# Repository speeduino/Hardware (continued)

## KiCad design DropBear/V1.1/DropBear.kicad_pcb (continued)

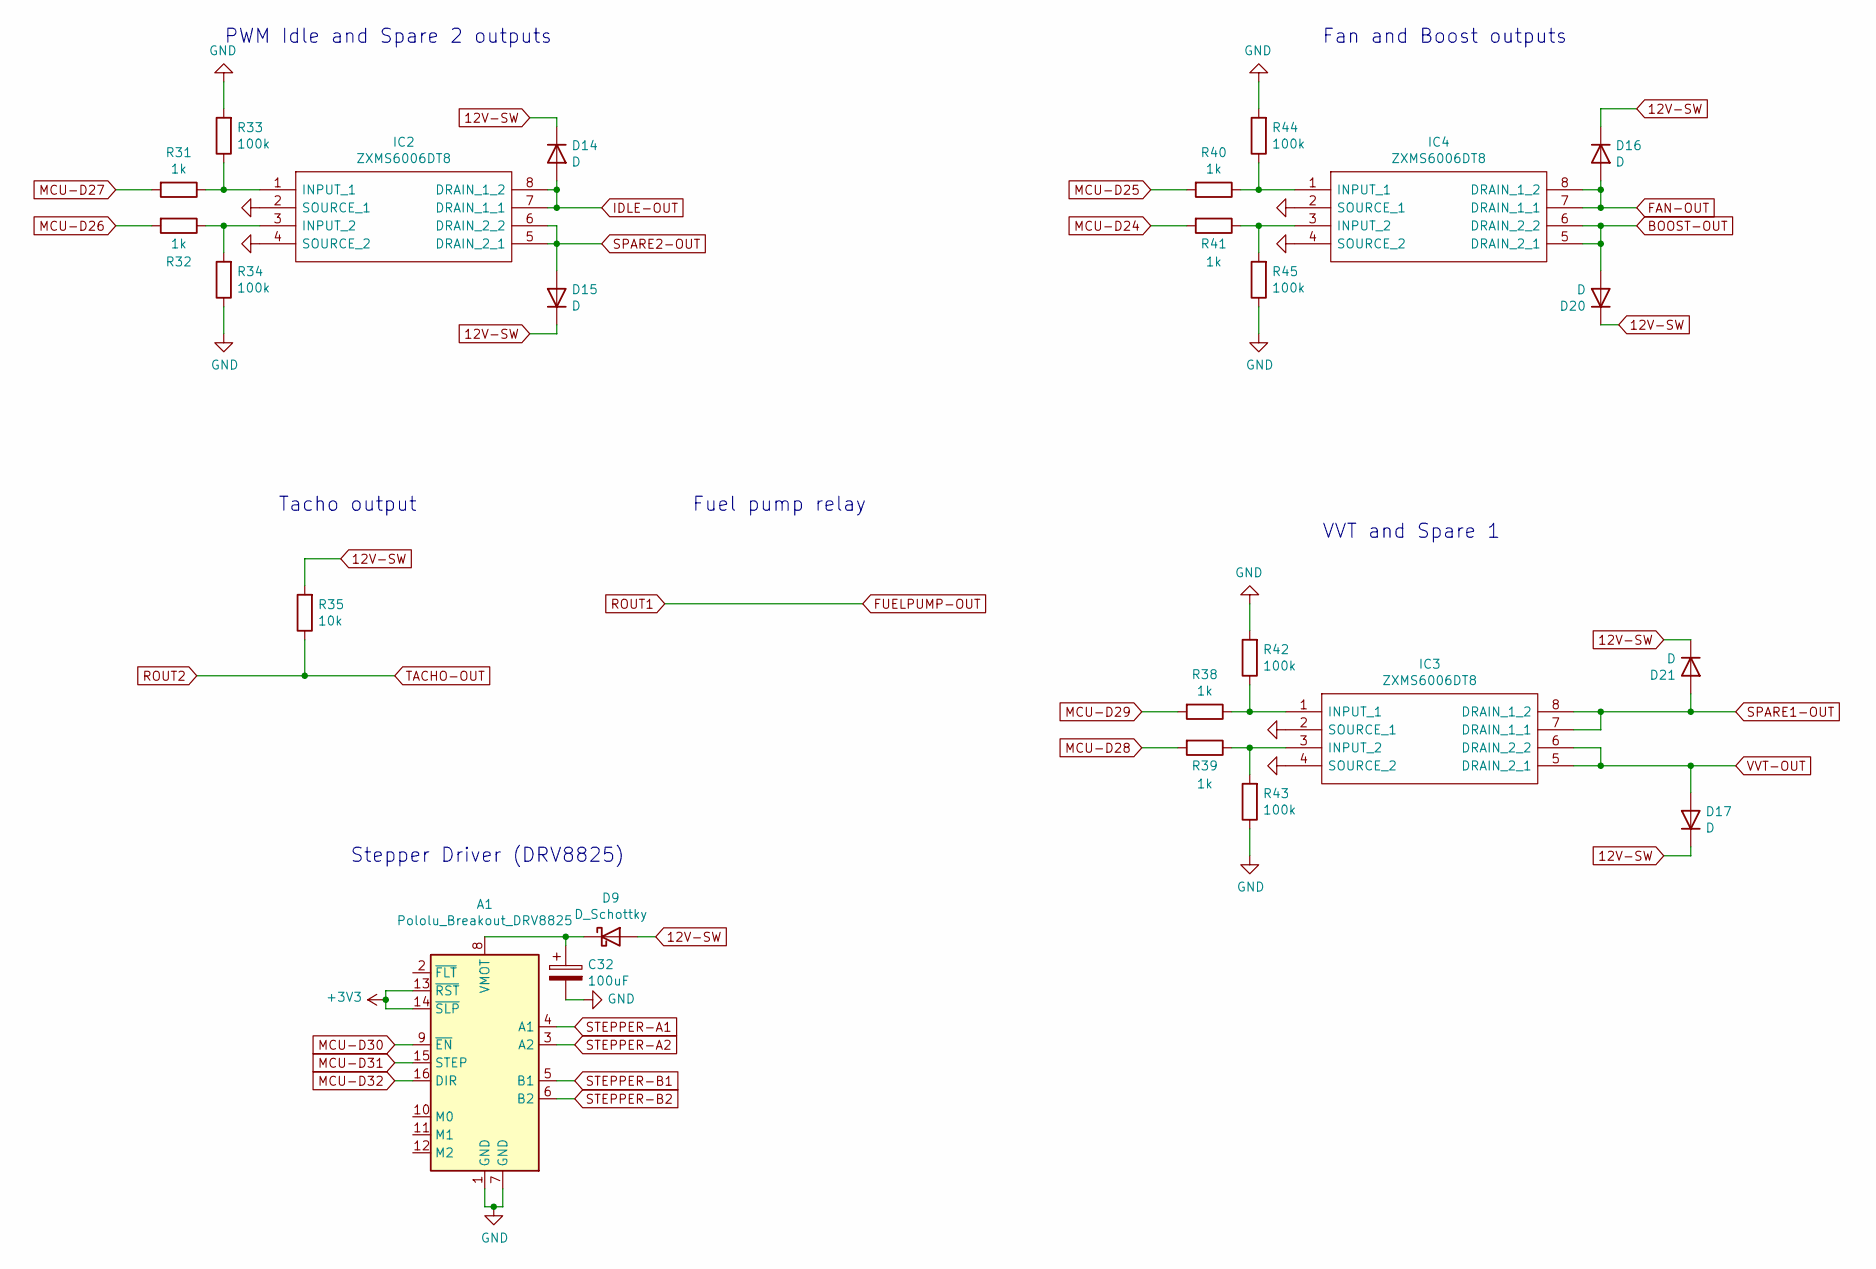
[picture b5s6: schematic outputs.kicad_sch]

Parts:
A1: Pololu_Breakout_DRV8825; Pololu_Breakout-16_15.2x20.3mm
C32: 100uF; CP_Elec_6.3x7.7; Manufacturer_Part_Number EEE-FT1V101AV; Digikey Part Number P124821CT-ND
D9: D_Schottky; D_PowerDI-123; Manufacturer_Part_Number DFLS2100-7; Digikey Part Number DFLS2100-7DICT-ND
D14, D15, D16, D17, D20, D21: D; D_SOD-323; Manufacturer_Part_Number 1N4448WX-TP; Digikey Part Number 1N4448WXTPMSCT-ND
IC2, IC3, IC4: ZXMS6006DT8; Diodes_SM8; Manufacturer_Part_Number ZXMS6006DT8; Digikey Part Number ZXMS6006DT8TADICT-ND
R31, R32, R38, R39, R40, R41: 1k; R_0805_2012Metric_Pad1.15x1.40mm_HandSolder; Manufacturer_Part_Number RC0805FR-071KL; Digikey Part Number 311-1.00KCRCT-ND
R33, R34, R42, R43, R44, R45: 100k; R_0805_2012Metric_Pad1.15x1.40mm_HandSolder; Manufacturer_Part_Number RC0805FR-07100KL; Digikey Part Number 311-100KCRCT-ND
R35: 10k; R_0805_2012Metric; Manufacturer_Part_Number RC0805JR-0710KL; Digikey Part Number 311-10KARCT-ND

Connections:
12V-SW: D9.2 (A), D14.1 (K), D15.1 (K), D16.1 (K), D17.1 (K), D20.1 (K), D21.1 (K), R35.2; also elsewhere on the board
+3V3: A1.13 (~RST), A1.14 (~SLP); also elsewhere on the board
BOOST-OUT: D20.2 (A), IC4.5 (DRAIN_2_1), IC4.6 (DRAIN_2_2); also elsewhere on the board
FAN-OUT: D16.2 (A), IC4.7 (DRAIN_1_1), IC4.8 (DRAIN_1_2); also elsewhere on the board
GND: A1.1 (GND), A1.7 (GND), C32.2, IC2.2 (SOURCE_1), IC2.4 (SOURCE_2), IC3.2 (SOURCE_1), IC3.4 (SOURCE_2), IC4.2 (SOURCE_1), IC4.4 (SOURCE_2), R33.2, R34.1, R42.2, R43.1, R44.2, R45.1; also elsewhere on the board
IDLE-OUT: A1.5 (B1), D14.2 (A), IC2.7 (DRAIN_1_1), IC2.8 (DRAIN_1_2); also elsewhere on the board
MCU-D24: R41.2; also elsewhere on the board
MCU-D25: R40.2; also elsewhere on the board
MCU-D26: R32.2; also elsewhere on the board
MCU-D27: R31.2; also elsewhere on the board
MCU-D28: R39.2; also elsewhere on the board
MCU-D29: R38.2; also elsewhere on the board
MCU-D30: A1.9 (~EN); also elsewhere on the board
MCU-D31: A1.15 (STEP); also elsewhere on the board
MCU-D32: A1.16 (DIR); also elsewhere on the board
unnamed: A1.8 (VMOT), C32.1, D9.1 (K)
unnamed: IC2.1 (INPUT_1), R31.1, R33.1
unnamed: IC2.3 (INPUT_2), R32.1, R34.2
unnamed: IC3.1 (INPUT_1), R38.1, R42.1
unnamed: IC3.3 (INPUT_2), R39.1, R43.2
unnamed: IC4.1 (INPUT_1), R40.1, R44.1
unnamed: IC4.3 (INPUT_2), R41.1, R45.2
ROUT2: R35.1; also elsewhere on the board
SPARE1-OUT: A1.3 (A2), D21.2 (A), IC3.7 (DRAIN_1_1), IC3.8 (DRAIN_1_2); also elsewhere on the board
SPARE2-OUT: A1.6 (B2), D15.2 (A), IC2.5 (DRAIN_2_1), IC2.6 (DRAIN_2_2); also elsewhere on the board
STEPPER-A1: A1.4 (A1), D17.2 (A), IC3.5 (DRAIN_2_1), IC3.6 (DRAIN_2_2); also elsewhere on the board

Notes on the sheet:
Fan and Boost outputs
Fuel pump relay
PWM Idle and Spare 2 outputs
Tacho output
VVT and Spare 1
Stepper Driver (DRV8825)

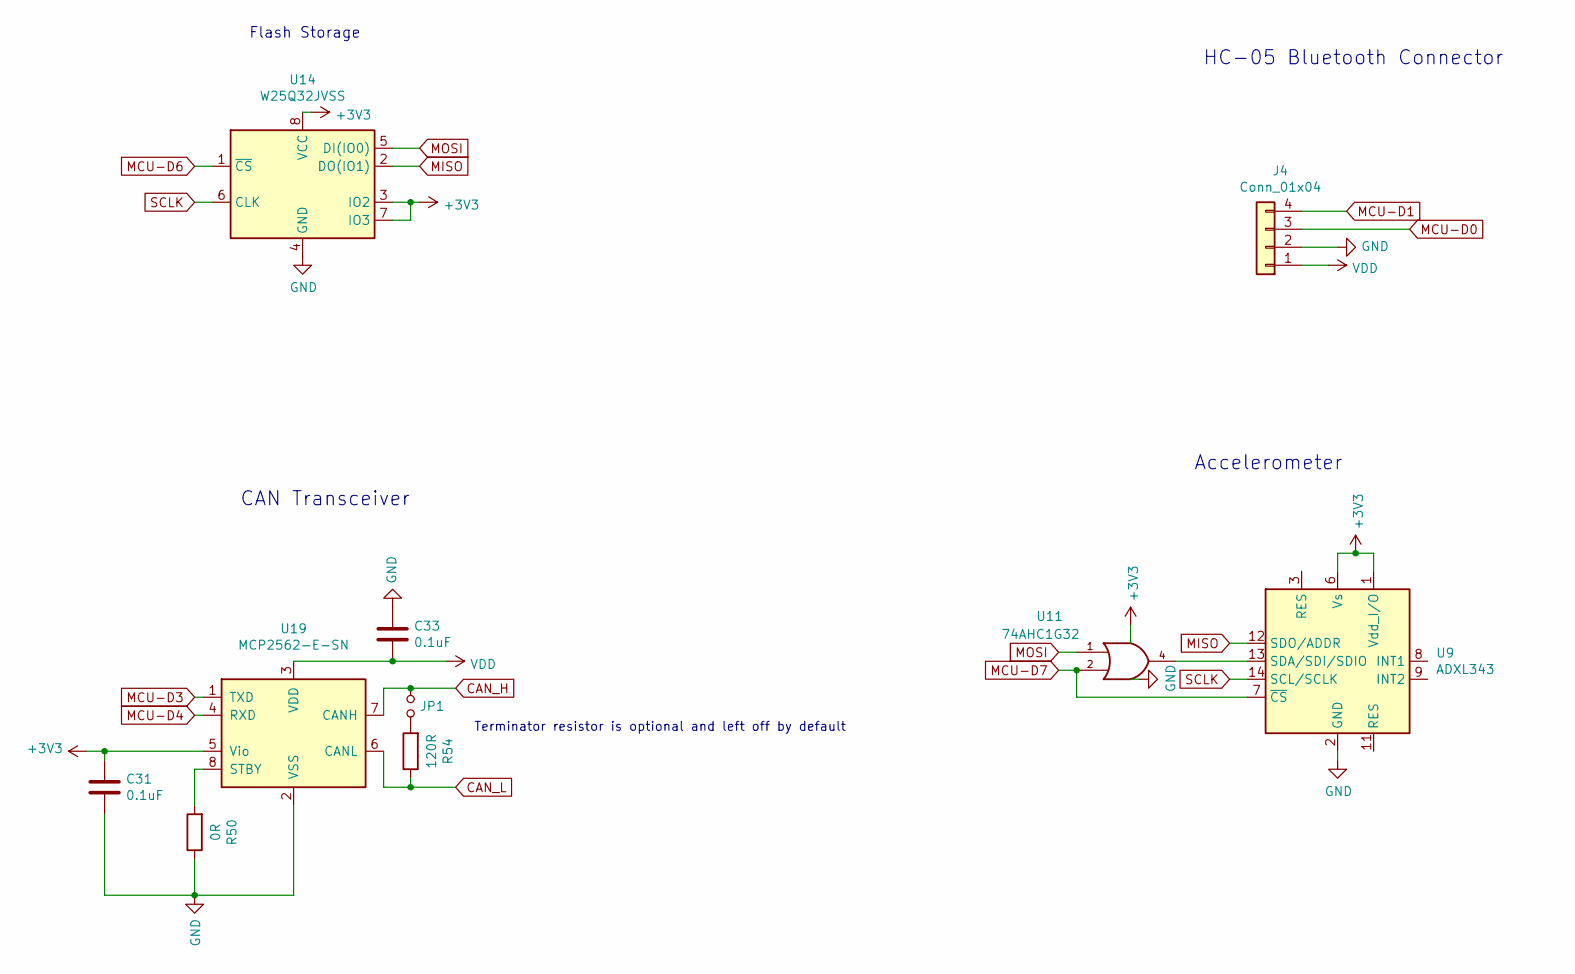
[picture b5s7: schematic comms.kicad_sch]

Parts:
C31, C33: 0.1uF; C_0805_2012Metric; Manufacturer_Part_Number CC0805KRX7R9BB104; Digikey Part Number 311-1140-1-ND
J4: Conn_01x04; PinHeader_1x04_P2.54mm_Vertical
JP1: Jumper_NO_Small; SolderJumper-2_P1.3mm_Open_Pad1.0x1.5mm
R50: 0R; R_0805_2012Metric_Pad1.15x1.40mm_HandSolder; Manufacturer_Part_Number RC0805JR-070RL; Digikey Part Number 311-0.0ARCT-ND
R54: 120R; R_0805_2012Metric_Pad1.15x1.40mm_HandSolder; Manufacturer_Part_Number RC0805FR-07120RL; Digikey Part Number 311-120CRCT-ND
U9: ADXL343; LGA-14_3x5mm_P0.8mm_LayoutBorder1x6y; Manufacturer_Part_Number ADXL343BCCZ-RL; Digikey Part Number ADXL343BCCZ-RLCT-ND
U11: 74AHC1G32; SOT-353_SC-70-5; Manufacturer_Part_Number SN74AHC1G32DCKR; Digikey Part Number 296-8749-1-ND
U14: W25Q32JVSS; SOIC-8_5.23x5.23mm_P1.27mm; Manufacturer_Part_Number W25Q32JVSSIQ; Digikey Part Number W25Q32JVSSIQCT-ND
U19: MCP2562-E-SN; SOIC-8_3.9x4.9mm_P1.27mm; Manufacturer_Part_Number MCP2562-E/SN; Digikey Part Number MCP2562-E/SN-ND

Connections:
+3V3: C31.1, U9.1 (Vdd_I/O), U9.6 (Vs), U11.5 (VCC), U14.3 (IO2), U14.7 (IO3), U14.8 (VCC), U19.5 (Vio); also elsewhere on the board
+5V: C33.2, J4.1, U19.3 (VDD); also elsewhere on the board
CAN_H: JP1.1, U19.7 (CANH); also elsewhere on the board
CAN_L: R54.1, U19.6 (CANL); also elsewhere on the board
GND: C31.2, C33.1, J4.2, R50.1, U9.2 (GND), U9.4 (GND), U9.5 (GND), U11.3 (GND), U14.4 (GND), U19.2 (VSS); also elsewhere on the board
MCU-D0: J4.3; also elsewhere on the board
MCU-D1: J4.4; also elsewhere on the board
MCU-D3: U19.1 (TXD); also elsewhere on the board
MCU-D4: U19.4 (RXD); also elsewhere on the board
MCU-D6: U14.1 (~CS); also elsewhere on the board
MCU-D7: U9.7 (~CS), U11.2; also elsewhere on the board
MISO: U9.12 (SDO/ADDR), U14.2 (DO(IO1)); also elsewhere on the board
MOSI: U11.1, U14.5 (DI(IO0)); also elsewhere on the board
unnamed: JP1.2, R54.2
unnamed: R50.2, U19.8 (STBY)
unnamed: U9.13 (SDA/SDI/SDIO), U11.4
SCLK: U9.14 (SCL/SCLK), U14.6 (CLK); also elsewhere on the board

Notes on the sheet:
Terminator resistor is optional and left off by default
Accelerometer
Flash Storage
CAN Transceiver
HC-05 Bluetooth Connector

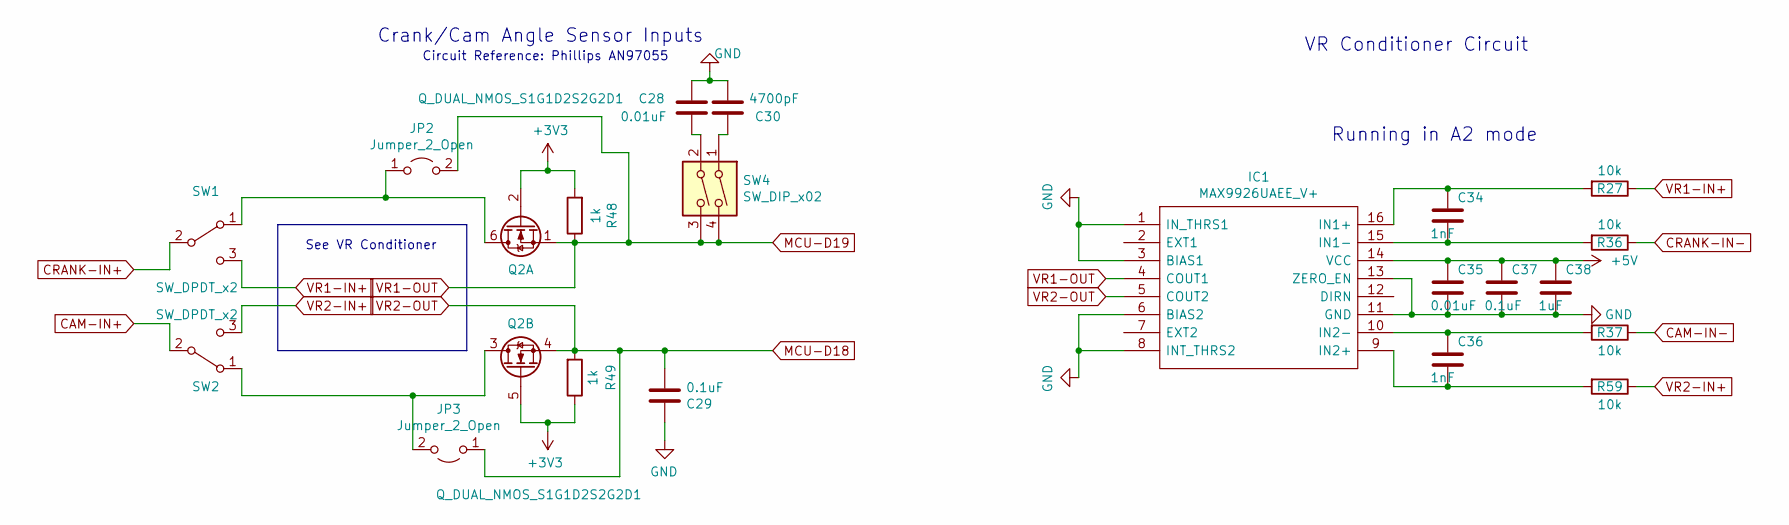
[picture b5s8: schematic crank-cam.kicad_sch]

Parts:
C28, C35: 0.01uF; C_0805_2012Metric; Manufacturer_Part_Number CC0805KRX7R9BB103; Digikey Part Number 311-1136-1-ND
C29, C37: 0.1uF; C_0805_2012Metric; Manufacturer_Part_Number CC0805KRX7R9BB104; Digikey Part Number 311-1140-1-ND
C30: 4700pF; C_0805_2012Metric; Manufacturer_Part_Number CC0805KRX7R9BB472; Digikey Part Number 311-1133-1-ND
C34, C36: 1nF; C_0805_2012Metric; Manufacturer_Part_Number C0805C102J5HACAUTO; Digikey Part Number 399-16591-1-ND
C38: 1uF; C_0805_2012Metric; Manufacturer_Part_Number CC0805KKX7R7BB105; Digikey Part Number 311-1365-1-ND
IC1: MAX9926UAEE_V+; QSOP-16_3.9x4.9mm_P0.635mm; Manufacturer_Part_Number MAX9926UAEE/V+; Mouser Part Number 700-MAX9926UAEE/V+
JP2, JP3: Jumper_2_Open; SolderJumper-2_P1.3mm_Open_Pad1.0x1.5mm
Q2: Q_DUAL_NMOS_S1G1D2S2G2D1; SOT-363_SC-70-6; Manufacturer_Part_Number NVJD5121NT1G; Digikey Part Number NVJD5121NT1GOSCT-ND
R27, R36, R37, R59: 10k; R_1206_3216Metric; Manufacturer_Part_Number RC1206FR-7W10KL; Digikey Part Number 13-RC1206FR-7W10KLTR-ND
R48, R49: 1k; R_0805_2012Metric; Manufacturer_Part_Number RC0805FR-071KL; Digikey Part Number 311-1.00KCRCT-ND
SW1, SW2: SW_DPDT_x2; AYZ0202AGRLC; Manufacturer_Part_Number AYZ0202AGRLC; Digikey Part Number 401-2013-1-ND
SW4: SW_DIP_x02; SW_DIP_SPSTx02_Slide_9.78x7.26mm_W8.61mm_P2.54mm; Manufacturer_Part_Number IKN0204000; Digikey Part Number 679-3566-1-ND

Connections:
+3V3: Q2.2 (G), Q2.5 (G), R48.2, R49.1; also elsewhere on the board
+5V: C35.1, C37.1, C38.1, IC1.14 (VCC); also elsewhere on the board
CAM-IN+: SW2.2 (B); also elsewhere on the board
CAM-IN-: R37.1; also elsewhere on the board
CRANK-IN+: SW1.2 (B); also elsewhere on the board
CRANK-IN-: R36.1; also elsewhere on the board
GND: C28.1, C29.1, C30.2, C35.2, C37.2, C38.2, IC1.1 (IN_THRS1), IC1.3 (BIAS1), IC1.6 (BIAS2), IC1.8 (INT_THRS2), IC1.11 (GND), IC1.13 (ZERO_EN); also elsewhere on the board
MCU-A4: C29.2, IC1.5 (COUT2), JP3.1 (A), Q2.4 (S), R49.2; also elsewhere on the board
MCU-A5: IC1.4 (COUT1), JP2.2 (B), Q2.1 (S), R48.1, SW4.3, SW4.4; also elsewhere on the board
unnamed: C28.2, SW4.2
unnamed: C30.1, SW4.1
unnamed: C34.1, IC1.16 (IN1+), R27.2
unnamed: C34.2, IC1.15 (IN1-), R36.2
unnamed: C36.1, IC1.10 (IN2-), R37.2
unnamed: C36.2, IC1.9 (IN2+), R59.2
unnamed: JP2.1 (A), Q2.6 (D), SW1.1 (A)
unnamed: JP3.2 (B), Q2.3 (D), SW2.1 (A)
VR1-IN+: R27.1, SW1.3 (C)
VR2-IN+: R59.1, SW2.3 (C)

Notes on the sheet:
Running in A2 mode
VR Conditioner Circuit
Crank/Cam Angle Sensor Inputs
See VR Conditioner
Circuit Reference: Phillips AN97055

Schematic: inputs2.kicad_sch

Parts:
C39, C40: 0.01uF; C_0805_2012Metric; Manufacturer_Part_Number CC0805KRX7R9BB103; Digikey Part Number 311-1136-1-ND
Q3: Q_DUAL_NMOS_S1G1D2S2G2D1; SOT-363_SC-70-6; Manufacturer_Part_Number NVJD5121NT1G; Digikey Part Number NVJD5121NT1GOSCT-ND
R55, R57: 180k; R_0805_2012Metric; Manufacturer_Part_Number RC0805FR-07180KL; Digikey Part Number 311-180KCRCT-ND
R56, R58: 348k; R_0805_2012Metric; Manufacturer_Part_Number ERJ-6ENF3483V; Digikey Part Number P348KCDKR-ND
R60, R61: 1k; R_0805_2012Metric; Manufacturer_Part_Number RC0805FR-071KL; Digikey Part Number 311-1.00KCRCT-ND
U20: LMV324LIDT; SOIC-14_3.9x8.7mm_P1.27mm; Manufacturer_Part_Number LMV324LIDT; Digikey Part Number 497-13052-1-ND

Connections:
+3V3: Q3.2 (G), Q3.5 (G), R60.2, R61.2; also elsewhere on the board
ADC-Clamp-3: U20.6 (-), U20.7; also elsewhere on the board
ADC-Clamp-4: U20.1, U20.2 (-); also elsewhere on the board
GND: C39.1, C40.1, R56.1, R58.1, U20.11 (V-); also elsewhere on the board
MCU-A8: C40.2, Q3.4 (S), R61.1; also elsewhere on the board
MCU-A9: C39.2, Q3.1 (S), R60.1; also elsewhere on the board
unnamed: R55.1, R56.2, U20.3 (+)
unnamed: R57.1, R58.2, U20.5 (+)
unnamed: U20.8, U20.9 (-)
unnamed: U20.13 (-), U20.14
SPARE1-Digital: Q3.6 (D); also elsewhere on the board
SPARE1_Sensor: R55.2; also elsewhere on the board
SPARE2-Digital: Q3.3 (D); also elsewhere on the board
SPARE2_Sensor: R57.2; also elsewhere on the board
VDDA: U20.4 (V+); also elsewhere on the board

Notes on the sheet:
5v to 3.3v Opamp
Second O2 sensor should be on Spare 2 if in use
Spare digital inputs

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
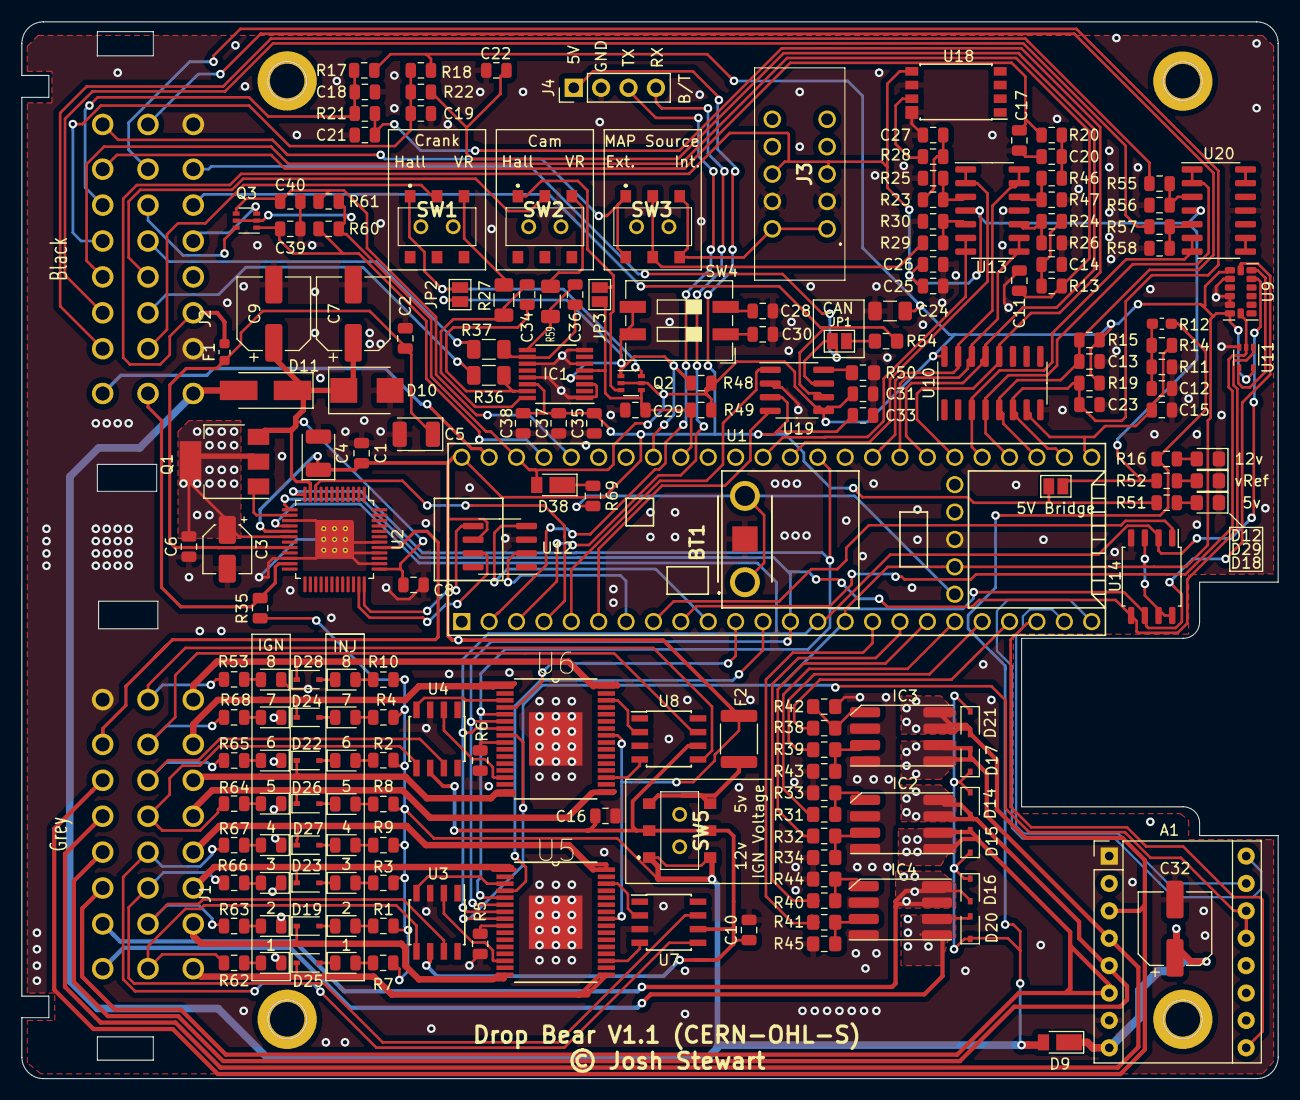
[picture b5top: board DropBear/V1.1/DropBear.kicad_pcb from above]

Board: 2 copper layers, 116.5 x 98.0 mm, 187 parts (0 on the bottom side), 165 nets.

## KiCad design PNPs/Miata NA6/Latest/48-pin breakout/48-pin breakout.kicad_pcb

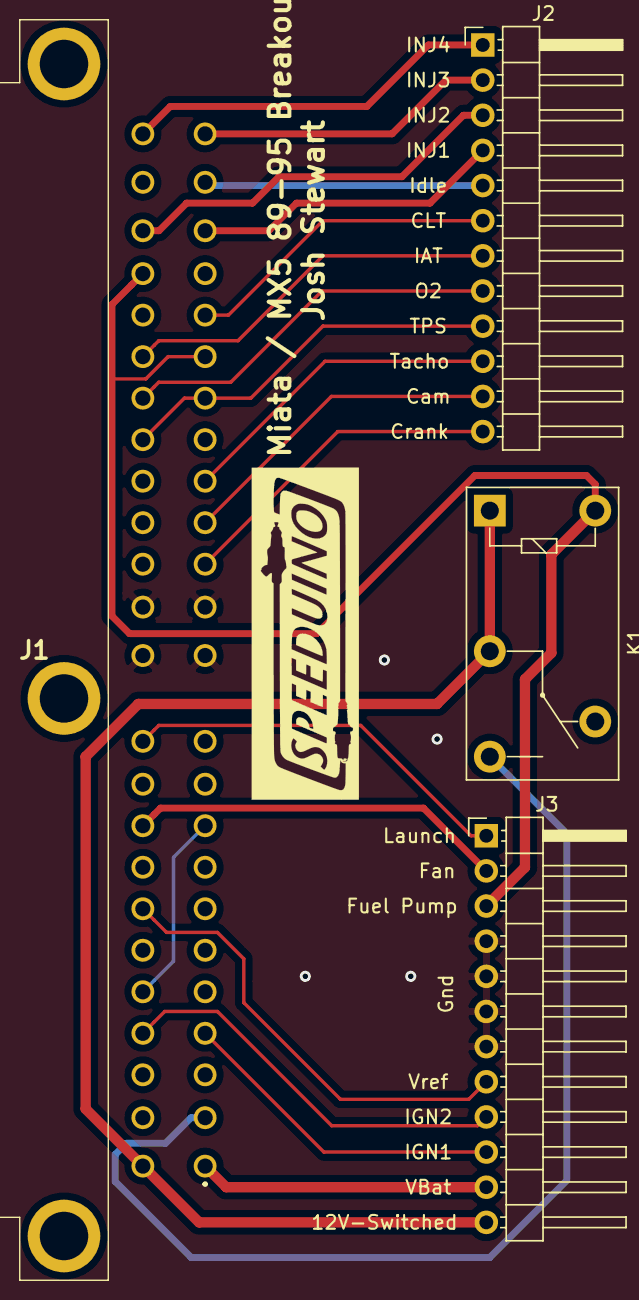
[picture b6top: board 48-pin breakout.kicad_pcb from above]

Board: 2 copper layers, 4 parts (0 on the bottom side), 23 nets.

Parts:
J1: 174917-1; 1749171
J2, J3: Conn_01x12; PinHeader_1x12_P2.54mm_Horizontal
K1: G5LE-1; Relay_SPDT_Omron-G5Q-1

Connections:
12V-SW: J1.25, J3.12, K1.1, K1.2
AC_Jump: J1.9, J1.29
CLT: J1.20, J2.6
Cam: J1.15, J2.11
Crank: J1.14, J2.12
Fan: J1.33, J3.2
GND: J1.12, J1.13, J1.36, J1.37, J3.4, J3.5, J3.6, J3.7
IAT: J1.43, J2.7
IGN-1: J1.4, J3.10
IGN-2: J1.28, J3.9
INJ-1: J1.22, J2.4
INJ-2: J1.46, J2.3
INJ-3: J1.24, J2.2
INJ-4: J1.48, J2.1
Idle: J1.23, J2.5
Launch: J1.35, J3.1
O2: J1.42, J2.8
Pump: J1.19, J1.45, J3.3, K1.5
ST_Sig: J1.2, K1.3
TPS: J1.18, J1.41, J2.9
Tacho: J1.16, J2.10
VBat: J1.1, J3.11
VRef: J1.31, J3.8

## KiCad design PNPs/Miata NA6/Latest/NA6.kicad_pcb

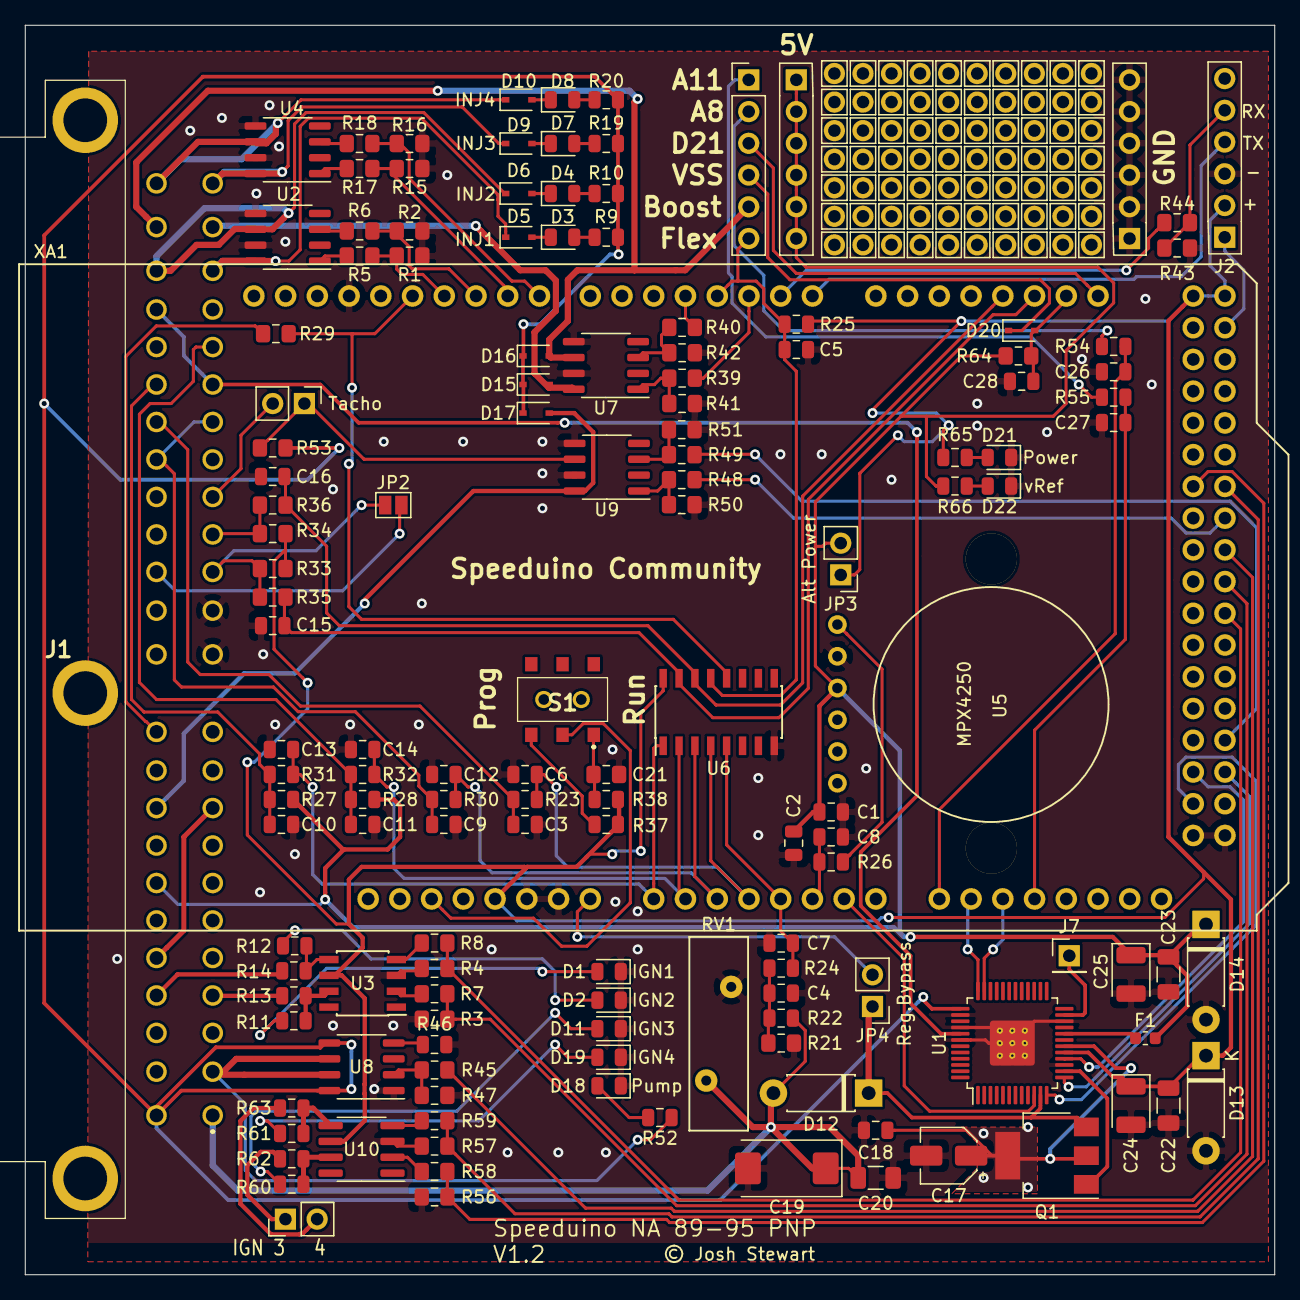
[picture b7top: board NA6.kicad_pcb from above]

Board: 2 copper layers, 100.0 x 100.0 mm, 142 parts (0 on the bottom side), 113 nets.

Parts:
C1: 0.01uF; C_0805_2012Metric
C2: 1uF; C_0805_2012Metric
C3, C4, C9, C10, C11, C15, C16, C18, C26, C27, C28: 0.1uF; C_0805_2012Metric
C5: 0.27uF; C_0805_2012Metric
C6, C7, C12, C13, C14: 0.22uF; C_0805_2012Metric
C8: 470pf; C_0805_2012Metric
C17: 22uF; CP_Elec_4x5.8
C19: 10uF; CP_EIA-7343-31_Kemet-D
C20, C22, C23: 0.1uF; C_1206_3216Metric
C21: 22uF; C_0805_2012Metric_Pad1.15x1.40mm_HandSolder
C24, C25: 47uF; CP_EIA-3528-21_Kemet-B
D1, D2, D3, D4, D7, D8, D11, D18, D19: LED; LED_0805_2012Metric
D5, D6, D9, D10, D15, D16, D17, D20: D; D_SOD-323
D12: D_Schottky; D_DO-41_SOD81_P7.62mm_Horizontal
D13, D14: D_Zener; D_DO-41_SOD81_P7.62mm_Horizontal
D21, D22: LED_Green; LED_0805_2012Metric
F1: Polyfuse; Fuse_0603_1608Metric
J1: 174917-1; 1749171
J2, J3, J4, J5: Conn_01x06; PinHeader_1x06_P2.54mm_Vertical
J6: Conn_01x02; PinHeader_1x02_P2.54mm_Vertical
J7: Conn_01x06; PinHeader_1x01_P2.54mm_Vertical
JP1: Jumper; PinHeader_1x02_P2.54mm_Vertical
JP2: Jumper; SolderJumper-2_P1.3mm_Open_Pad1.0x1.5mm
JP3, JP4: Jumper_2_Open; PinHeader_1x02_P2.54mm_Vertical
Q1: Q_PNP_BCEC; SOT-223-3_TabPin2
R1, R2, R3, R4, R15, R16, R41, R42, R47, R50, R51, R56, R57: 100k; R_0805_2012Metric_Pad1.15x1.40mm_HandSolder
R5, R6, R7, R8, R17, R18, R21, R29, R33, R34, R39, R40, R44, R45, R48, R49, R53, R58, R59, R64: 1k; R_0805_2012Metric_Pad1.15x1.40mm_HandSolder
R9, R10, R11, R12, R19, R20, R25, R60, R61: 2.4k; R_0805_2012Metric
R13, R14, R62, R63: 10R; R_0805_2012Metric
R22: 3.9k; R_0805_2012Metric
R23, R24, R26, R30, R31, R32, R54, R55, R65, R66: 470R; R_0805_2012Metric
R27, R28, R52: 2.49k; R_0805_2012Metric
R35, R36: 220R; R_0805_2012Metric_Pad1.15x1.40mm_HandSolder
R37, R46: 10k; R_0805_2012Metric
R38: 120R; R_0805_2012Metric
R43: 2k; R_0805_2012Metric_Pad1.15x1.40mm_HandSolder
RV1: Varistor; RV_Disc_D15.5mm_W4.7mm_P7.5mm
S1: AYZ0202AGRLC
U1: MC33814; LQFP-48-1EP_7x7mm_P0.5mm_EP3.6x3.6mm_ThermalVias
U2, U4, U7, U9: VNLD5090; SO-8_3.9x4.9mm_P1.27mm
U3, U10: TC4424A; SOIC-8_3.9x4.9mm_P1.27mm
U5: MPX4250
U6: SP720; SOIC-16_3.9x9.9mm_P1.27mm
U8: VN5160S-E; SO-8_3.9x4.9mm_P1.27mm
XA1: Arduino_Mega2560_Shield; Arduino_Mega2560_Shield_IO_Only

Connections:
12V-SW: D15.1, D16.1, D17.1, J1.25, R9.2, R10.2, R19.2, R20.2, R53.1, U1.37, U8.5, U8.8
33814-CSB: U1.10, XA1.A6
AC-Jump: J1.9, J1.29
ADC-Clamp-1: C13.1, R31.1, U6.1, XA1.A0
ADC-Clamp-2: C14.1, R32.1, U6.2, XA1.A1
ADC-Clamp-3: C12.1, R30.1, U6.3, XA1.A2
ADC-Clamp-4: C6.1, R23.1, U6.4, XA1.A3
ADC-Clamp-5: C7.1, R24.1, U6.5, XA1.A4
ADC-Clamp-11: R29.2, U6.12, XA1.D12
ADC-Clamp-12: C5.1, J5.6, R25.2, U6.13, XA1.D3
ADC-Clamp-13: C16.2, R36.1, U6.14, XA1.D18
ADC-Clamp-14: C15.2, R35.1, U6.15, XA1.D19
BOOST-OUT: D16.2, J1.47, J5.5, U7.6
CAM-IN: J1.15, R34.1, R36.2
CLT_Sensor: C11.1, J1.20, R28.1, R32.2
CRANK-IN: J1.14, JP2.1, R33.1, R35.2
Clutch_in: J1.35, R29.1
FAN-OUT: D17.2, J1.33, U9.8
GND: C1.1, C2.1, C3.2, C4.2, C5.2, C6.2, C7.2, C8.1, C9.2, C10.2, C11.2, C12.2, C13.2, C14.2, C15.1, C16.1, C17.2, C18.2, C19.2, C20.2, C21.2, C22.2, C23.2, C24.2, C25.2, C26.2, C27.2, C28.2, D1.1, D2.1, D11.1, D13.2, D14.2, D18.1, D19.1, D21.1, D22.1, J1.12, J1.13, J1.36, J1.37, J2.3, J4.1, J4.2, J4.3, J4.4, J4.5, J4.6, R1.2, R2.1, R3.2, R4.1, R15.2, R16.1, R21.1, R41.2, R42.1, R43.2, R46.2, R47.2, R50.2, R51.1, R56.2, R57.1, RV1.2, U1.15, U1.22, U1.38, U1.40, U1.42, U1.49, U2.5, U2.7, U3.3, U4.5, U4.7, U5.2, U6.8, U7.5, U7.7, U8.1, U9.5, U9.7, U10.3, XA1.GND1, XA1.GND2, XA1.GND3, XA1.GND5, XA1.GND6
IAT_Sensor: C10.1, J1.43, R27.1, R31.2
IDLE-OUT: D15.2, J1.23, U7.8
IGN-1-OUT: J1.4, R13.1
IGN-2-OUT: J1.28, R14.1
IGN-3-OUT: J6.1, R62.1
IGN-4-OUT: J6.2, R63.1
INJ-1-OUT: D5.1, J1.22, U2.8
INJ-2-OUT: D6.1, J1.46, U2.6
INJ-3-OUT: D9.1, J1.24, U4.8
INJ-4-OUT: D10.1, J1.48, U4.6
MCU-A5: C8.2, R26.1, XA1.A5
MCU-A8: C26.1, R54.2, XA1.A8
MCU-A9: U1.36, XA1.A9
MCU-A10: U1.35, XA1.A10
MCU-A11: C27.1, R55.1, XA1.A11
MCU-D0: J2.4, XA1.D0
MCU-D1: R44.1, XA1.D1
MCU-D2: R39.2, XA1.D2
MCU-D4: R40.2, XA1.D4
MCU-D8: R16.2, R18.2, XA1.D8
MCU-D9: R15.1, R17.2, XA1.D9
MCU-D10: R2.2, R6.2, XA1.D10
MCU-D11: R1.1, R5.2, XA1.D11
MCU-D20: C28.1, D20.2, R64.2, XA1.D20
MCU-D21: J5.3, XA1.D21
MCU-D23: J2.1, XA1.D23
MCU-D32: R56.1, R58.2, XA1.D32
MCU-D33: R57.2, R59.2, XA1.D33
MCU-D35: R48.2, XA1.D35
MCU-D37: R45.2, XA1.D37
MCU-D39: R3.1, R7.2, XA1.D39
MCU-D41: R4.2, R8.2, XA1.D41
MCU-D49: R49.2, XA1.D49
MCU-D50: U1.16, XA1.D50
MCU-D51: U1.13, XA1.D51
MCU-D52: U1.12, XA1.D52
unnamed: C4.1, R21.2, R22.1, R24.2
unnamed: C21.1, R38.1, S1.1
unnamed: D1.2, R11.2
unnamed: D2.2, R12.2
unnamed: D3.1, D5.2
unnamed: D3.2, R9.1
unnamed: D4.1, D6.2
unnamed: D4.2, R10.1
unnamed: D7.1, D9.2
unnamed: D7.2, R19.1
unnamed: D8.2, R20.1
unnamed: D8.1, D10.2
unnamed: D11.2, R60.2
unnamed: D18.2, R52.2
unnamed: D19.2, R61.2
unnamed: D21.2, R65.1
unnamed: D22.2, R66.1
unnamed: F1.1, U1.20
unnamed: J1.38, JP2.2
unnamed: J2.5, R43.1, R44.2
unnamed: J5.1, R55.2
unnamed: J5.2, R54.1
unnamed: JP1.1, R53.2, U9.6
unnamed: R5.1, U2.1
unnamed: R6.1, U2.3
unnamed: R7.1, U3.2
unnamed: R8.1, U3.4
unnamed: R11.1, R13.2, U3.7
unnamed: R12.1, R14.2, U3.5
unnamed: R17.1, U4.1
unnamed: R18.1, U4.3
unnamed: R26.2, U5.1
unnamed: R37.1, S1.3
unnamed: R39.1, R41.1, U7.1
unnamed: R40.1, R42.2, U7.3
unnamed: R45.1, R47.1, U8.2
unnamed: R46.1, U8.4
unnamed: R48.1, R50.1, U9.1
unnamed: R49.1, R51.2, U9.3
unnamed: R58.1, U10.2
unnamed: R59.1, U10.4
unnamed: R60.1, R62.2, U10.7
unnamed: R61.1, R63.2, U10.5
O2_Sensor: C3.1, J1.42, R23.2
RESET: S1.2, XA1.RST1
ROUT1: J1.19, J1.45, U1.41
ROUT2: J7.1, U1.23
ST_Sig: J1.2, R52.1, U8.6, U8.7
TACHO-OUT: J1.16, JP1.2
TPS_Sensor: C9.1, J1.18, J1.41, R30.2
VBat: C19.1, C20.1, D12.2, J1.1, R22.2, RV1.1
VDD: C22.1, C24.1, D13.1, J2.2, JP3.1, R25.1, R33.2, R34.2, R37.2, R38.2, R65.2, U1.17, U3.6, U6.16, U10.6, XA1.5V1, XA1.5V3, XA1.5V4
VDDA: C1.2, C2.2, C23.1, C25.1, D14.1, F1.2, J1.31, J3.1, J3.2, J3.3, J3.4, J3.5, J3.6, JP3.2, R27.2, R28.2, R64.1, R66.2, U5.3
VIN: JP4.2, XA1.VIN
VPPREF: Q1.1, U1.14
VPPSENS: C17.1, C18.1, Q1.2, U1.18
VRegIn: D12.1, JP4.1, Q1.3, U1.11
VSS: D20.1, J5.4

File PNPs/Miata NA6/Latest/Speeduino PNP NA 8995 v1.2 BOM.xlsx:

Reference | Quantity | Value | Footprint | Manufacturer_Name | Manufacturer_Part_Number | URL | Digikey Part Number | Comment
C1 | 1 | 0.01uF | Capacitor_SMD:C_0805_2012Metric | Yageo | CC0805KRX7R9BB103 | https://www.digikey.com/product-detail/en/yageo/CC0805KRX7R9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 | 311-1136-1-ND
C17 | 1 | 22uF | Capacitor_SMD:CP_Elec_4x5.8 | Panasonic | EEE-FK0J220R | https://www.digikey.com/product-detail/en/panasonic-electron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 | PCE3765CT-ND
C19 | 1 | 10uF | Capacitor_Tantalum_SMD:CP_EIA-7343-31_Kemet-D | Kemet | T491D106K050AT | https://www.digikey.com/product-detail/en/kemet/T491D106K050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 | 399-8361-1-ND
C2 | 1 | 1uF | Capacitor_SMD:C_0805_2012Metric | Yageo | CC0805KKX7R7BB105 | https://www.digikey.com/product-detail/en/yageo/CC0805KKX7R7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 | 311-1365-1-ND
C20 C22 C23 | 3 | 0.1uF | Capacitor_SMD:C_1206_3216Metric | Kemet | C1206C104K5RAC7867 | https://www.digikey.com/product-detail/en/kemet/C1206C104K5R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 | 399-1249-1-ND
C21 | 1 | 22uF | Capacitor_SMD:C_0805_2012Metric_Pad1.15x1.40mm_HandSolder | Samsung | CL21A226KQCLRNC | https://www.digikey.com.au/product-detail/en/samsung-electro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 | 1276-6687-1-ND
C24 C25 | 2 | 47uF | Capacitor_Tantalum_SMD:CP_EIA-3528-21_Kemet-B | AVX | TAJB476K006RNJ | https://www.digikey.com/product-detail/en/avx-corporation/TA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 | 478-1692-1-ND
C3 C9 C10 C11 C4 C15 C16 C18 C27 C26 C28 | 11 | 0.1uF | Capacitor_SMD:C_0805_2012Metric | Yageo | CC0805KRX7R9BB104 | https://www.digikey.com.au/product-detail/en/yageo/CC0805KRX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 | 311-1140-1-ND
C5 | 1 | 0.27uF | Capacitor_SMD:C_0805_2012Metric | Yageo | CC0805JRX7R7BB274 | https://www.digikey.com.au/product-detail/en/yageo/CC0805JRX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 | 311-4268-1-ND
C6 C12 C13 C14 C7 | 5 | 0.22uF | Capacitor_SMD:C_0805_2012Metric | Samsung | CL21B224KOCNNNC | https://www.digikey.com/product-detail/en/samsung-electro-me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 | 1276-1284-1-ND
C8 | 1 | 470pf | Capacitor_SMD:C_0805_2012Metric | Yageo | CC0805KRX7R9BB471 | https://www.digikey.com/product-detail/en/yageo/CC0805KRX7R9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 | 311-1124-1-ND
D10 D9 D5 D6 D16 D15 D17 D20 | 8 | D | Diode_SMD:D_SOD-323 | Micro Commercial Co | 1N4448WX-TP | https://www.digikey.com/product-detail/en/micro-commercial-c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 | 1N4448WXTPMSCT-ND
D12 | 1 | D_Schottky | Diode_THT:D_DO-41_SOD81_P7.62mm_Horizontal | Micro Commercial Co | 1N5818-TP | https://www.digikey.com/product-detail/en/micro-commercial-c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 | 1N5818-TPCT-ND
D22 D21 | 2 | LED_Green | LED_SMD:LED_0805_2012Metric | Osram | LG R971-KN-1 | https://www.digikey.com/product-detail/en/osram-opto-semicon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 | 475-1410-1-ND
D4 D3 D8 D7 D1 D2 D11 D19 D18 | 9 | LED | LED_SMD:LED_0805_2012Metric | Osram | LH R974-LP-1 | https://www.digikey.com/product-detail/en/osram-opto-semicon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 | 475-1415-1-ND
F1 | 1 | Polyfuse | Fuse:Fuse_0603_1608Metric | Bel Fuse | 0ZCM0008FF2G | https://www.digikey.com.au/product-detail/en/bel-fuse-inc/0Z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 | 507-1817-1-ND
J1 | 1 | 174917-1 | Connector_Automotive:1749171 | TE Connectivity | 174917-1 | https://au.rs-online.com/web/p/pcb-connector-housings/720100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
Q1 | 1 | Q_PNP_BCEC | Package_TO_SOT_SMD:SOT-223-3_TabPin2 | Diodes Inc | FZT753TA | https://www.digikey.com.au/product-detail/en/diodes-incorpor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 | FZT753CT-ND
R1 R2 R15 R16 R3 R4 R56 R57 R42 R41 R51 R50 R47 | 13 | 100k | Resistor_SMD:R_0805_2012Metric_Pad1.15x1.40mm_HandSolder | Yageo | RC0805FR-07100KL | https://www.digikey.com/product-detail/en/yageo/RC0805FR-071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 | 311-100KCRCT-ND
R10 R9 R20 R19 R11 R12 R60 R61 R25 | 9 | 2.4k | Resistor_SMD:R_0805_2012Metric | Yageo | RC0805FR-072K4L | https://www.digikey.com/product-detail/en/yageo/RC0805FR-072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 | 311-2.40KCRCT-ND
R13 R14 R62 R63 | 4 | 10R | Resistor_SMD:R_0805_2012Metric | Yageo | RC0805FR-0710RL | https://www.digikey.com/product-detail/en/yageo/RC0805FR-071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 | 311-10.0CRCT-ND
R22 | 1 | 3.9k | Resistor_SMD:R_0805_2012Metric | Yageo | RC0805FR-073K9L | https://www.digikey.com/product-detail/en/yageo/RC0805FR-073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 | 311-3.90KCRCT-ND
R26 R23 R30 R31 R32 R24 R66 R65 R55 R54 R65 R66 | 12 | 470R | Resistor_SMD:R_0805_2012Metric | Panasonic | ERJ-6ENF4700V | https://www.digikey.com/product-detail/en/panasonic-electron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 | P470CCT-ND
R27 R28 R52 | 3 | 2.49k | Resistor_SMD:R_0805_2012Metric | Yageo | RT0805BRD072K49L | https://www.digikey.com/product-detail/en/yageo/RT0805BRD072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 | YAG1854CT-ND
R35 R36 | 2 | 220R | Resistor_SMD:R_0805_2012Metric_Pad1.15x1.40mm_HandSolder | Yageo | RC0805FR-07220RL | https://www.digikey.com/product-detail/en/yageo/RC0805FR-072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 | 311-220CRCT-ND
R37 R46 | 2 | 10k | Resistor_SMD:R_0805_2012Metric | Yageo | RC0805JR-0710KL | https://www.digikey.com/product-detail/en/yageo/RC0805JR-071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 | 311-10KARCT-ND
R38 | 1 | 120R | Resistor_SMD:R_0805_2012Metric | Yageo | RC0805FR-07120RL | https://www.digikey.com/product-detail/en/yageo/RC0805FR-071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 | 311-120CRCT-ND
R43 | 1 | 2k | Resistor_SMD:R_0805_2012Metric_Pad1.15x1.40mm_HandSolder | Yageo | RC0805FR-072KL | https://www.digikey.com/product-detail/en/yageo/RC0805FR-072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 | 311-2.00KCRCT-ND
R5 R6 R17 R18 R7 R8 R58 R59 R21 R29 R33 R34 R39 R40 R48 R49 R44 R45 R53 R64 | 20 | 1k | Resistor_SMD:R_0805_2012Metric_Pad1.15x1.40mm_HandSolder | Yageo | RC0805FR-071KL | https://www.digikey.com/product-detail/en/yageo/RC0805FR-071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 | 311-1.00KCRCT-ND
RV1 | 1 | Varistor | Varistor:RV_Disc_D15.5mm_W4.7mm_P7.5mm | Bourns Inc | MOV-14D220K | https://www.digikey.com.au/product-detail/en/bourns-inc/MOV-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 | MOV-14D220K-ND
S1 | 1 | AYZ0202AGRLC | AYZ0202AGRLC | C & K COMPONENTS | AYZ0202AGRLC | https://www.digikey.com.au/product-detail/en/c-k/AYZ0202AGRL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 | 401-2013-1-ND
U1 | 1 | MC33814 | Package_QFP:LQFP-48-1EP_7x7mm_P0.5mm_EP3.6x3.6mm_ThermalVias | NCP | MC33814 | http://au.element14.com/nxp/mc33814ae/ic-control-1-cylinder-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
U2 U4 U7 U9 | 4 | VNLD5090 | Package_SO:SO-8_3.9x4.9mm_P1.27mm | STMicro | VNLD5090-E | https://mouser.com/search/ProductDetail.aspx?R=0virtualkey0v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 | 497-18682-ND
U3 U10 | 2 | TC4424A | Package_SO:SOIC-8_3.9x4.9mm_P1.27mm | Microchip | TC4424AVOA | https://www.digikey.com/product-detail/en/microchip-technolo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 | TC4424AVOA-ND
U5 | 1 | MPX4250 | Misc:MPX4250 | NXP | MPX4250AP | https://www.digikey.com.au/product-detail/en/nxp-usa-inc/MPX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 | MPX4250AP-ND
U6 | 1 | SP720 | Package_SO:SOIC-16_3.9x9.9mm_P1.27mm | Littelfuse | SP720ABTG | https://www.digikey.com/product-detail/en/littelfuse-inc/SP7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 | F3162CT-ND
U8 | 1 | VN5160S-E | Package_SO:SO-8_3.9x4.9mm_P1.27mm | STMicro | VN5160S-E | https://www.digikey.com.au/products/en?keywords=VN5160S-E | 497-19720-ND
XA1 | 4 | Arduino_Mega2560 header pins | CONN HEADER .100" SNGL STR 40POS | Sullins Connector Solutions | PREC040SAAN-RC | https://www.digikey.com.au/products/en?keywords=S1012EC-40-ND |  | Pins attach to bottom of board

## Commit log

2021-05-13 Initial commit of the v0.3.x boards
2021-05-13 Add v0.4.3d and NA6 PNP
2021-06-05 Add most of the remaining boards
2021-06-14 Folder cleanup
2021-06-23 Add schematic for v0.4.3d
2021-06-23 Add v0.4.4c files
2021-06-23 Minor fix for v0.4.4c
2021-07-12 Add diagrams and PCB images for older PNP boards
2021-11-07 Added files for constructing a PNP case, pulled from commit 1f8b8eb4 of noisymime/speeduino
2022-08-07 Improve silk screen labeling & ground plane. Added solder pads.
2023-01-22 v3.74 corrects channel 1 polarity, improves silkscreen & makes solderability of PTH bits
    Polarity in previous version not critical as everyone seems to try their pick-up each way anyhow.
2023-05-09 Update README references to Discord
2023-05-12 Add v0.4.4d SMD design files
2023-05-22 NA6 PNP v1.3 files
2023-07-24 Add Dropbear v1.1 design files
2023-07-25 Fix for unconnected ground on 1 capacitor
2023-07-25 Minor conversion corrections on Dropbear PCB
2023-08-01 Add PDF schematic for Dropbear
2024-08-07 Update v0.4.3d.kicad_pcb
    fixed Q5 and Q6 to use TO-220 packages
2024-08-07 updated Q5 and Q6 to use TO-220 package
    Q5 and Q6 used an outdated component that is no longer in production.
    Updated components to use TO-220 packages which are more readily available.
2024-08-07 updated to version 0.4.3e
    updated Q5 and Q6 to TO-220 packages, and updated BOM to use new TO-220 substitute.
    Version D Q5 and Q6 used a dip4 which was discontinued and no longer available.
2024-10-08 Add end plates for NA6 PNP
2025-03-09 Cleanup and remove rescue dependencies
2026-02-07 Add Dropbear v2.0.1
2026-02-07 V0.3 MAP card
2026-02-08 Add schematic pdf for Dropbear v2.0.1
2026-02-08 Cleanup and revised gitignore
